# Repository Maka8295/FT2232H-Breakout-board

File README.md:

# Bill of Materials

**Line items:** 28  |  **Total components:** 70

> Pin header connectors (J2–J12) are excluded from this BOM.

## IC

| Designator | Value / Part | Footprint | Qty |
|---|---|---|---|
| U1 | LDK130M18R | `SOT-23-5` | 1 |
| U2 | LDK130M25R | `SOT-23-5` | 1 |
| U3 | AP2112K-3.3 | `SOT-23-5` | 1 |
| U4 | USBLC6-2SC6 | `SOT-23-6` | 1 |
| U5 | 93LCxxBxxOT | `SOT-23-6` | 1 |
| U6 | FT2232HL | `LQFP-64_10x10mm_P0.5mm` | 1 |
| U7, U8 | TMUX1574DYY | `Texas_DYY0016A_TSOT-23-16_2x4.2mm_P0.5mm` | 2 |
| U9, U10 | SN74LVC8T245PWR | `TSSOP-24_4.4x7.8mm_P0.65mm` | 2 |

## Connector

| Designator | Value / Part | Footprint | Qty |
|---|---|---|---|
| J1 | USB_A | `USB_A_CNCTech_1001-011-01101_Horizontal` | 1 |

## Resistor

| Designator | Value / Part | Footprint | Qty |
|---|---|---|---|
| R1 | 2.2k | `R_0603_1608Metric_Pad0.98x0.95mm` | 1 |
| R2, R3, R5 | 1k | `R_0603_1608Metric_Pad0.98x0.95mm` | 3 |
| R4 | 1M | `R_0603_1608Metric_Pad0.98x0.95mm` | 1 |
| R6 | 12k/1% | `R_0603_1608Metric_Pad0.98x0.95mm` | 1 |
| R7, R8, R9, R10 | 4.7k | `R_0603_1608Metric_Pad0.98x0.95mm` | 4 |
| R11, R12, R13 | 10k | `R_0603_1608Metric_Pad0.98x0.95mm` | 3 |
| R14 | 2k | `R_0603_1608Metric_Pad0.98x0.95mm` | 1 |

## Capacitor

| Designator | Value / Part | Footprint | Qty |
|---|---|---|---|
| C1, C2, C3, C4, C5, C6 | 1uF | `C_0603_1608Metric_Pad1.08x0.95mm` | 6 |
| C7 | 2.2nF | `C_0603_1608Metric_Pad1.08x0.95mm` | 1 |
| C8, C10 | 10nF | `C_0603_1608Metric_Pad1.08x0.95mm` | 2 |
| C9 | 100nF | `C_0603_1608Metric_Pad1.08x0.95mm` | 1 |
| C11, C12, C13, C14, C15, C18, C19, C20, C22, C24, C27, C28, C29, C31, C33, C34, C35, C36, C37, C39 | 0.1uF | `C_0603_1608Metric_Pad1.08x0.95mm` | 20 |
| C16 | 0.01uF | `C_0603_1608Metric_Pad1.08x0.95mm` | 1 |
| C17, C21, C23, C30, C32, C38 | 4.7uF | `C_0603_1608Metric_Pad1.08x0.95mm` | 6 |

## Inductor

| Designator | Value / Part | Footprint | Qty |
|---|---|---|---|
| L1, L2, L3 | 600R/0.5A | `L_0603_1608Metric_Pad1.05x0.95mm` | 3 |

## Transistor/MOSFET

| Designator | Value / Part | Footprint | Qty |
|---|---|---|---|
| Q1 | AO3400A | `SOT-23` | 1 |

## LED

| Designator | Value / Part | Footprint | Qty |
|---|---|---|---|
| D1, D2 | LED | `LED_0603_1608Metric` | 2 |

## Crystal

| Designator | Value / Part | Footprint | Qty |
|---|---|---|---|
| Y1 | SCTF SX3M12.000M20F30TNN | `Crystal_SMD_3225-4Pin_3.2x2.5mm_HandSoldering` | 1 |

## Switch

| Designator | Value / Part | Footprint | Qty |
|---|---|---|---|
| SW1 | Reset Button | `SW_Push_1P1T_NO_CK_KMR2` | 1 |

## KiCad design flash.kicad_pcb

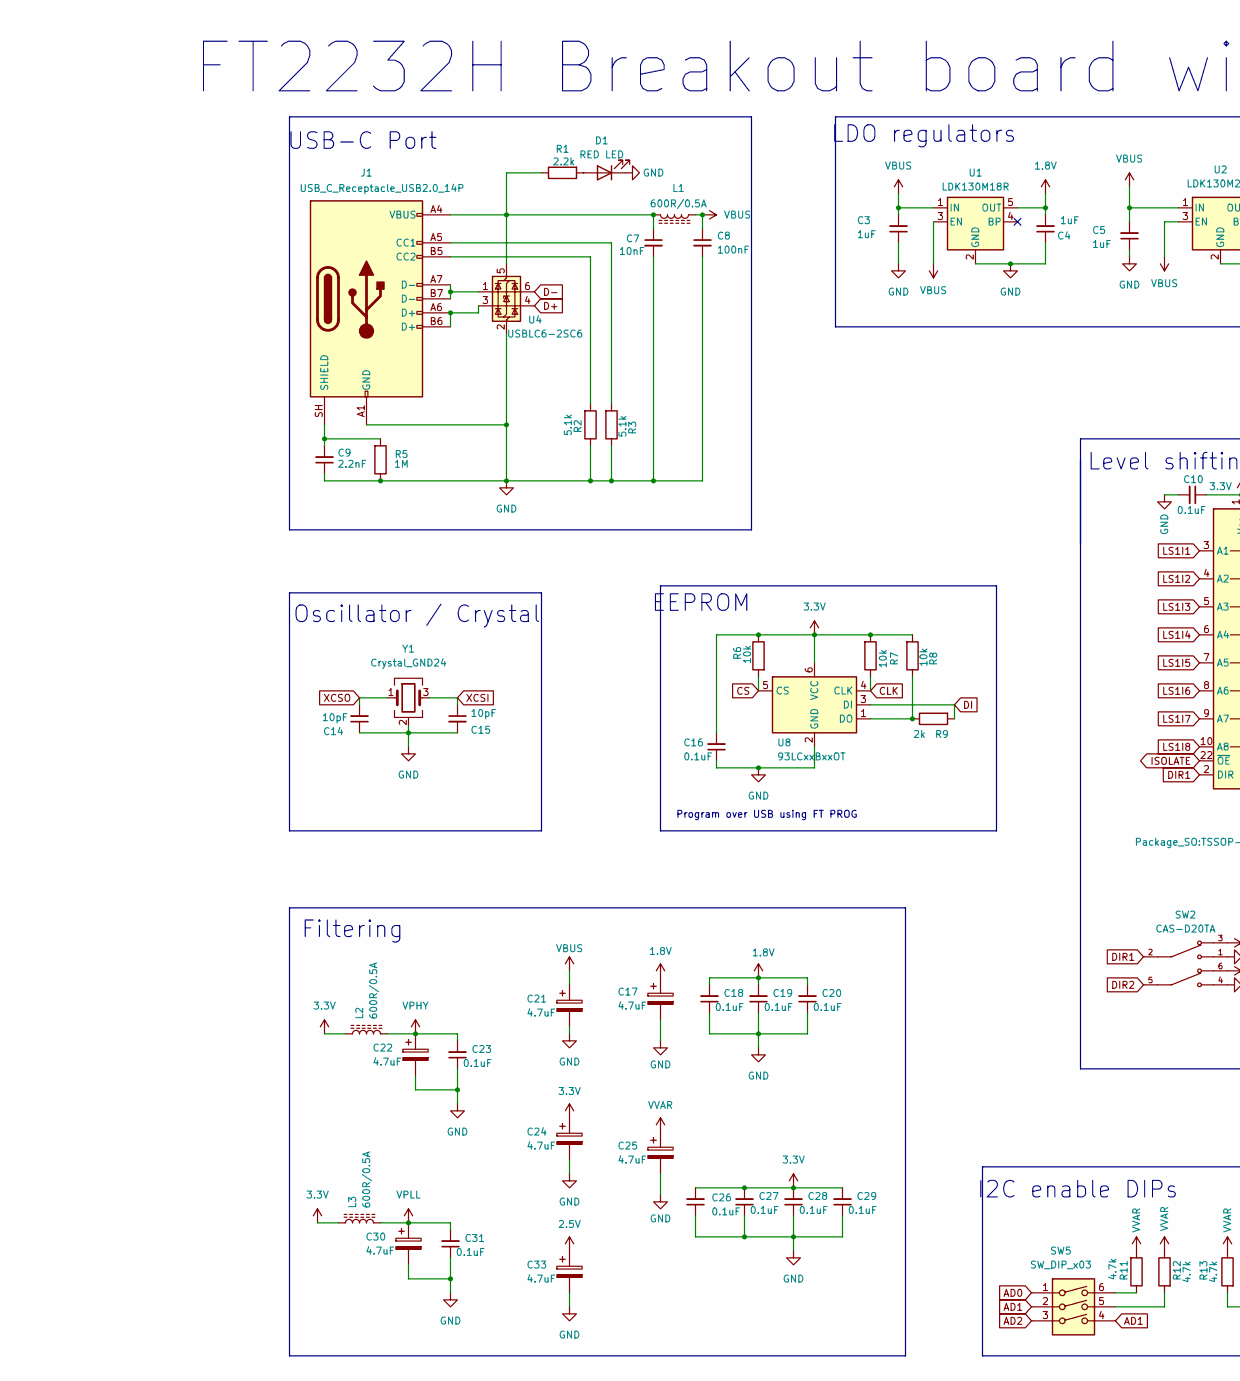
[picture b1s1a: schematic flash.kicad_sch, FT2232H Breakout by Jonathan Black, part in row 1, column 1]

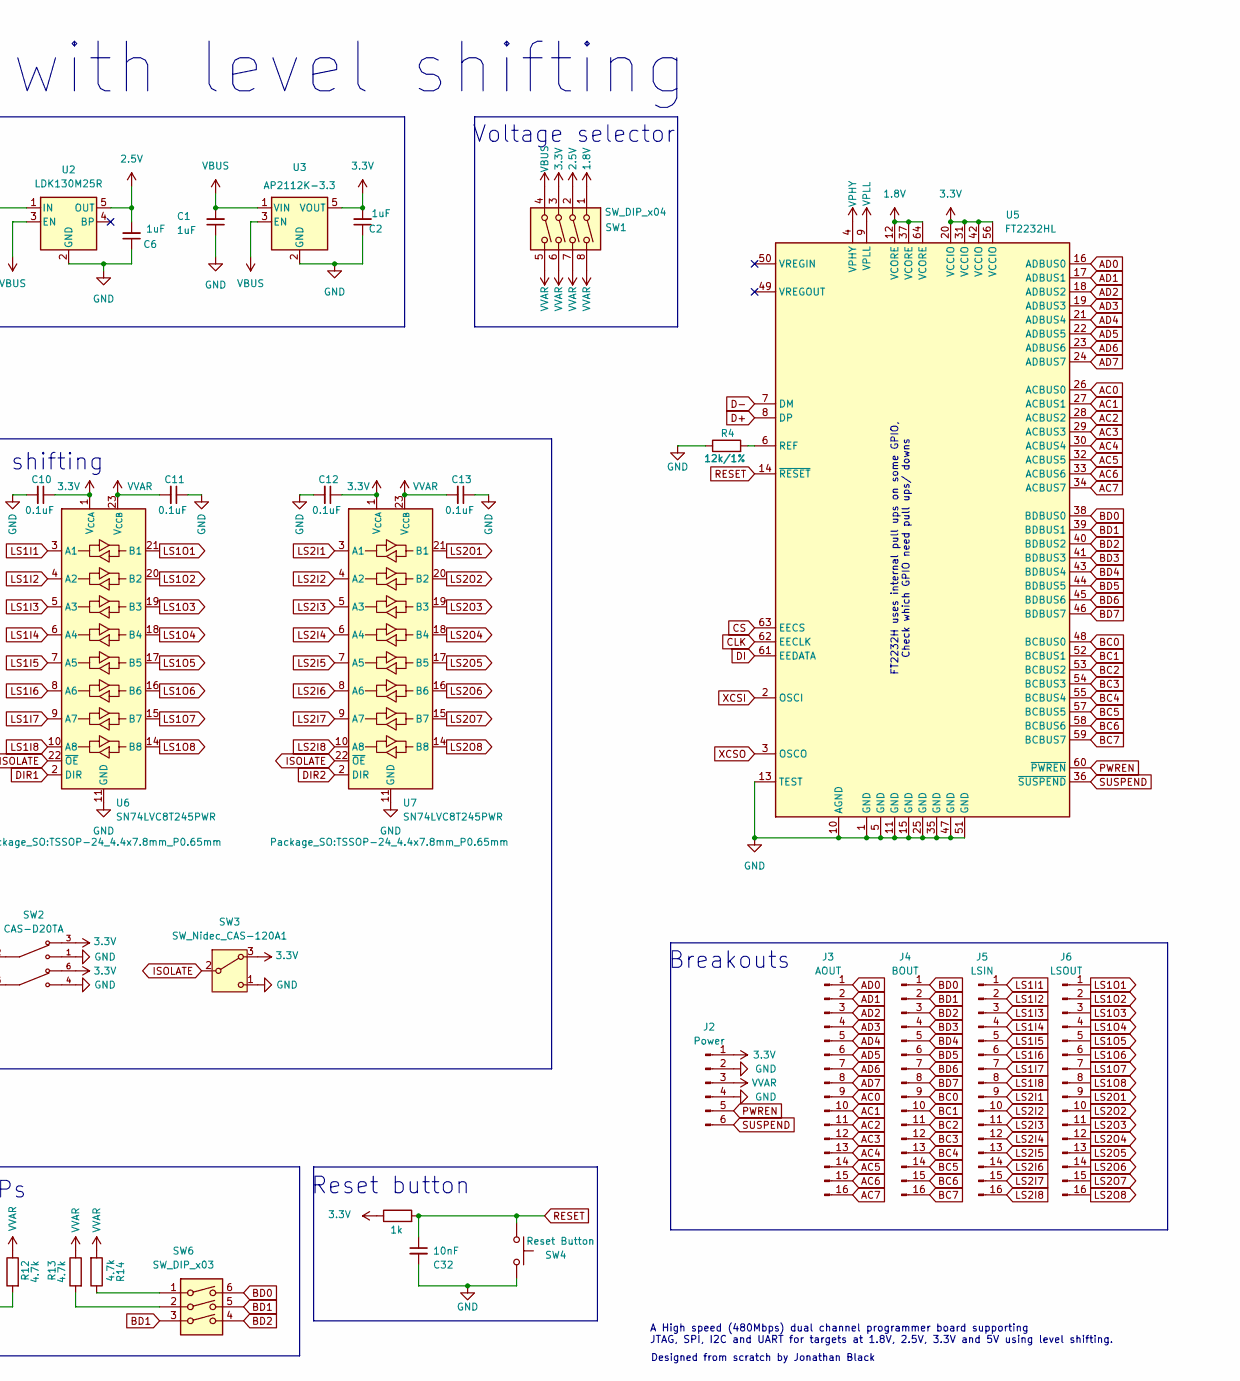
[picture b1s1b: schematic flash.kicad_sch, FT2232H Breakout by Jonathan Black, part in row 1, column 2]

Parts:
C1, C2, C3, C4, C5, C6: 1uF; C_0603_1608Metric_Pad1.08x0.95mm_HandSolder
C7, C32: 10nF; C_0603_1608Metric_Pad1.08x0.95mm_HandSolder
C8: 100nF; C_0603_1608Metric_Pad1.08x0.95mm_HandSolder
C9: 2.2nF; C_0603_1608Metric_Pad1.08x0.95mm_HandSolder
C10, C11, C12, C13, C16, C18, C19, C20, C23, C26, C27, C28, C29, C31: 0.1uF; C_0603_1608Metric_Pad1.08x0.95mm_HandSolder
C14, C15: 10pF; C_0603_1608Metric_Pad1.08x0.95mm_HandSolder
C17, C21, C22, C24, C25, C30, C33: 4.7uF; C_0603_1608Metric_Pad1.08x0.95mm_HandSolder
D1: RED LED; LED_0603_1608Metric
J1: USB_C_Receptacle_USB2.0_14P; USB_C_Receptacle_HRO_TYPE-C-31-M-12
J2: Power; PinHeader_2x03_P2.54mm_Vertical
J3: AOUT; PinHeader_1x16_P2.54mm_Vertical
J4: BOUT; PinHeader_1x16_P2.54mm_Vertical
J5: LSIN; PinHeader_2x08_P2.54mm_Vertical
J6: LSOUT; PinHeader_2x08_P2.54mm_Vertical
L1, L2, L3: 600R/0.5A; L_0603_1608Metric_Pad1.05x0.95mm_HandSolder
R1: 2.2k; R_0603_1608Metric_Pad0.98x0.95mm_HandSolder
R2, R3: 5.1k; R_0603_1608Metric_Pad0.98x0.95mm_HandSolder
R4: 12k/1%; R_0603_1608Metric_Pad0.98x0.95mm_HandSolder
R5: 1M; R_0603_1608Metric_Pad0.98x0.95mm_HandSolder
R6, R7, R8: 10k; R_0603_1608Metric_Pad0.98x0.95mm_HandSolder
R9: 2k; R_0603_1608Metric_Pad0.98x0.95mm_HandSolder
R10: 1k; R_0603_1608Metric_Pad0.98x0.95mm_HandSolder
R11, R12, R13, R14: 4.7k; R_0603_1608Metric_Pad0.98x0.95mm_HandSolder
SW1: SW_DIP_x04; SW_DIP_SPSTx04_Slide_Copal_CHS-04A_W5.08mm_P1.27mm_JPin
SW2: CAS-D20TA; SW_CAS-D20TA; PARTREV N/A
SW3: SW_Nidec_CAS-120A1; Nidec_Copal_CAS-120A
SW4: Reset Button; SW_Push_1P1T_NO_CK_KMR2
SW5, SW6: SW_DIP_x03; SW_DIP_SPSTx03_Slide_KingTek_DSHP03TJ_W5.25mm_P1.27mm_JPin
U1: LDK130M18R; SOT-23-5
U2: LDK130M25R; SOT-23-5
U3: AP2112K-3.3; SOT-23-5
U4: USBLC6-2SC6; SOT-23-6
U5: FT2232HL; LQFP-64_10x10mm_P0.5mm
U6, U7: SN74LVC8T245PWR; TSSOP-24_4.4x7.8mm_P0.65mm
U8: 93LCxxBxxOT; SOT-23-6
Y1: Crystal_GND24; Crystal_SMD_3225-4Pin_3.2x2.5mm_HandSoldering

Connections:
1.8V: C4.2, C17.1, C18.2, C19.2, C20.2, SW1.1, U1.5 (OUT), U5.12 (VCORE), U5.37 (VCORE), U5.64 (VCORE)
2.5V: C6.2, C33.1, SW1.2, U2.5 (OUT)
3.3V: C2.2, C10.1, C12.1, C16.2, C24.1, C26.2, C27.2, C28.2, C29.2, J2.1, L2.1, L3.1, R6.1, R7.2, R8.2, R10.1, SW1.3, SW2.3, SW2.6, SW3.3 (A), U3.5 (VOUT), U5.20 (VCCIO), U5.31 (VCCIO), U5.42 (VCCIO), U5.56 (VCCIO), U6.1 (V_{CCA}), U7.1 (V_{CCA}), U8.6 (VCC)
AC0: J3.9, U5.26 (ACBUS0)
AC1: J3.10, U5.27 (ACBUS1)
AC2: J3.11, U5.28 (ACBUS2)
AC3: J3.12, U5.29 (ACBUS3)
AC4: J3.13, U5.30 (ACBUS4)
AC5: J3.14, U5.32 (ACBUS5)
AC6: J3.15, U5.33 (ACBUS6)
AC7: J3.16, U5.34 (ACBUS7)
AD0: J3.1, SW5.1, U5.16 (ADBUS0)
AD1: J3.2, SW5.2, SW5.4, U5.17 (ADBUS1)
AD2: J3.3, SW5.3, U5.18 (ADBUS2)
AD3: J3.4, U5.19 (ADBUS3)
AD4: J3.5, U5.21 (ADBUS4)
AD5: J3.6, U5.22 (ADBUS5)
AD6: J3.7, U5.23 (ADBUS6)
AD7: J3.8, U5.24 (ADBUS7)
BC0: J4.9, U5.48 (BCBUS0)
BC1: J4.10, U5.52 (BCBUS1)
BC2: J4.11, U5.53 (BCBUS2)
BC3: J4.12, U5.54 (BCBUS3)
BC4: J4.13, U5.55 (BCBUS4)
BC5: J4.14, U5.57 (BCBUS5)
BC6: J4.15, U5.58 (BCBUS6)
BC7: J4.16, U5.59 (BCBUS7)
BD0: J4.1, SW6.6, U5.38 (BDBUS0)
BD1: J4.2, SW6.3, SW6.5, U5.39 (BDBUS1)
BD2: J4.3, SW6.4, U5.40 (BDBUS2)
BD3: J4.4, U5.41 (BDBUS3)
BD4: J4.5, U5.43 (BDBUS4)
BD5: J4.6, U5.44 (BDBUS5)
BD6: J4.7, U5.45 (BDBUS6)
BD7: J4.8, U5.46 (BDBUS7)
CLK: R7.1, U5.62 (EECLK), U8.4 (CLK)
CS: R6.2, U5.63 (EECS), U8.5 (CS)
D+: U4.4 (I/O2), U5.8 (DP)
D-: U4.6 (I/O1), U5.7 (DM)
DI: R9.2, U5.61 (EEDATA), U8.3 (DI)
DIR1: SW2.2, U6.2 (DIR)
DIR2: SW2.5, U7.2 (DIR)
GND: C1.1, C2.1, C3.1, C4.1, C5.1, C6.1, C7.2, C8.2, C9.1, C10.2, C11.1, C12.2, C13.1, C14.1, C15.2, C16.1, C17.2, C18.1, C19.1, C20.1, C21.2, C22.2, C23.1, C24.2, C25.2, C26.1, C27.1, C28.1, C29.1, C30.2, C31.1, C32.2, C33.2, D1.1 (K), J1.A1 (GND), J1.A12 (GND), J1.B1 (GND), J1.B12 (GND), J2.2, J2.4, R2.1, R3.1, R4.1, R5.1, SW2.1, SW2.4, SW3.1 (C), SW4.2, U1.2 (GND), U2.2 (GND), U3.2 (GND), U4.2 (GND), U5.1 (GND), U5.5 (GND), U5.10 (AGND), U5.11 (GND), U5.13 (TEST), U5.15 (GND), U5.25 (GND), U5.35 (GND), U5.47 (GND), U5.51 (GND), U6.11 (GND), U6.12 (GND), U6.13 (GND), U7.11 (GND), U7.12 (GND), U7.13 (GND), U8.2 (GND), Y1.2 (G), Y1.4 (G)
ISOLATE: SW3.2 (B), U6.22 (~OE), U7.22 (~OE)
LS1I1: J5.1, U6.3 (A1)
LS1I2: J5.2, U6.4 (A2)
LS1I3: J5.3, U6.5 (A3)
LS1I4: J5.4, U6.6 (A4)
LS1I5: J5.5, U6.7 (A5)
LS1I6: J5.6, U6.8 (A6)
LS1I7: J5.7, U6.9 (A7)
LS1I8: J5.8, U6.10 (A8)
LS1O1: J6.1, U6.21 (B1)
LS1O2: J6.2, U6.20 (B2)
LS1O3: J6.3, U6.19 (B3)
LS1O4: J6.4, U6.18 (B4)
LS1O5: J6.5, U6.17 (B5)
LS1O6: J6.6, U6.16 (B6)
LS1O7: J6.7, U6.15 (B7)
LS1O8: J6.8, U6.14 (B8)
LS2I1: J5.9, U7.3 (A1)
LS2I2: J5.10, U7.4 (A2)
LS2I3: J5.11, U7.5 (A3)
LS2I4: J5.12, U7.6 (A4)
LS2I5: J5.13, U7.7 (A5)
LS2I6: J5.14, U7.8 (A6)
LS2I7: J5.15, U7.9 (A7)
LS2I8: J5.16, U7.10 (A8)
LS2O1: J6.9, U7.21 (B1)
LS2O2: J6.10, U7.20 (B2)
LS2O3: J6.11, U7.19 (B3)
LS2O4: J6.12, U7.18 (B4)
LS2O5: J6.13, U7.17 (B5)
LS2O6: J6.14, U7.16 (B6)
LS2O7: J6.15, U7.15 (B7)
LS2O8: J6.16, U7.14 (B8)
unnamed: D1.2 (A), R1.2
unnamed: J1.A5 (CC1), R3.2
unnamed: J1.B5 (CC2), R2.2
unnamed: J1.A6 (D+), J1.B6 (D+), U4.3 (I/O2)
unnamed: J1.A7 (D-), J1.B7 (D-), U4.1 (I/O1)
unnamed: C9.2, J1.SH (SHIELD), R5.2
unnamed: R11.1, SW5.6
unnamed: R12.2, SW5.5
unnamed: R13.2, SW6.2
unnamed: R14.1, SW6.1
unnamed: C7.1, J1.A4 (VBUS), J1.A9 (VBUS), J1.B4 (VBUS), J1.B9 (VBUS), L1.2, R1.1, U4.5 (VBUS)
unnamed: R4.2, U5.6 (REF)
unnamed: R8.1, R9.1, U8.1 (DO)
PWREN: J2.5, U5.60 (~PWREN)
RESET: C32.1, R10.2, SW4.1, U5.14 (~RESET)
SUSPEND: J2.6, U5.36 (~SUSPEND)
VBUS: C1.2, C3.2, C5.2, C8.1, C21.1, L1.1, SW1.4, U1.1 (IN), U1.3 (EN), U2.1 (IN), U2.3 (EN), U3.1 (VIN), U3.3 (EN)
VPHY: C22.1, C23.2, L2.2, U5.4 (VPHY)
VPLL: C30.1, C31.2, L3.2, U5.9 (VPLL)
VVAR: C11.2, C13.2, C25.1, J2.3, R11.2, R12.1, R13.1, R14.2, SW1.5, SW1.6, SW1.7, SW1.8, U6.23 (V_{CCB}), U6.24 (V_{CCB}), U7.23 (V_{CCB}), U7.24 (V_{CCB})
XCSI: C15.1, U5.2 (OSCI), Y1.3
XCSO: C14.2, U5.3 (OSCO), Y1.1

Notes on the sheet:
Breakouts
Level shifting
Reset button
I2C enable DIPs
FT2232H Breakout board with level shifting
FT2232H uses internal pull ups on some GPIO, Check which GPIO need pull ups/ downs
Designed from scratch by Jonathan Black
Filtering
USB-C Port
Voltage selector
Program over USB using FT PROG
A High speed (480Mbps) dual channel programmer board supporting JTAG, SPI, I2C and UART for targets at 1.8V, 2.5V, 3.3V and 5V using level shifting.
Oscillator / Crystal
EEPROM
LDO regulators

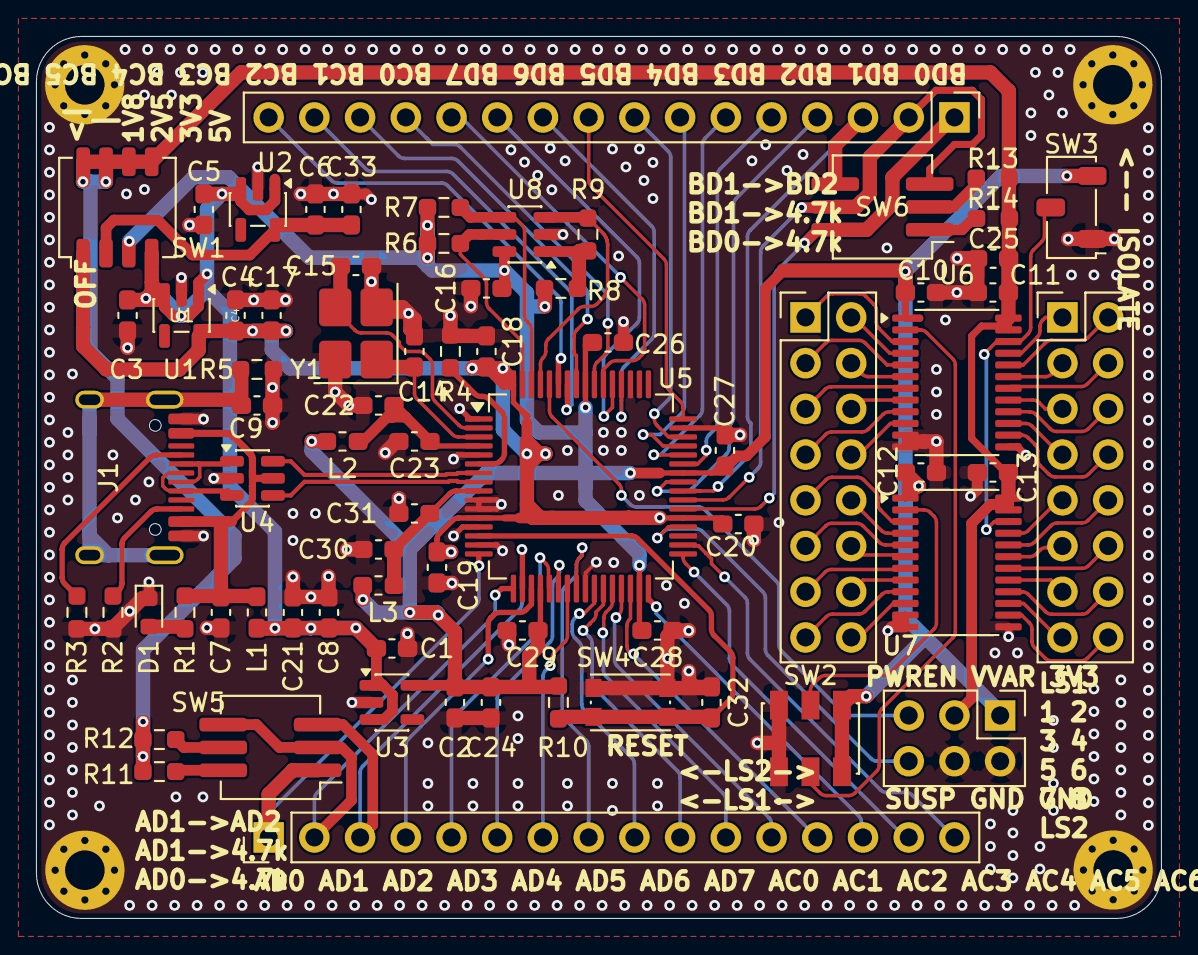
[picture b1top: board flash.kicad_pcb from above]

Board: 4 copper layers, 62.5 x 49.0 mm, 72 parts (0 on the bottom side), 98 nets.

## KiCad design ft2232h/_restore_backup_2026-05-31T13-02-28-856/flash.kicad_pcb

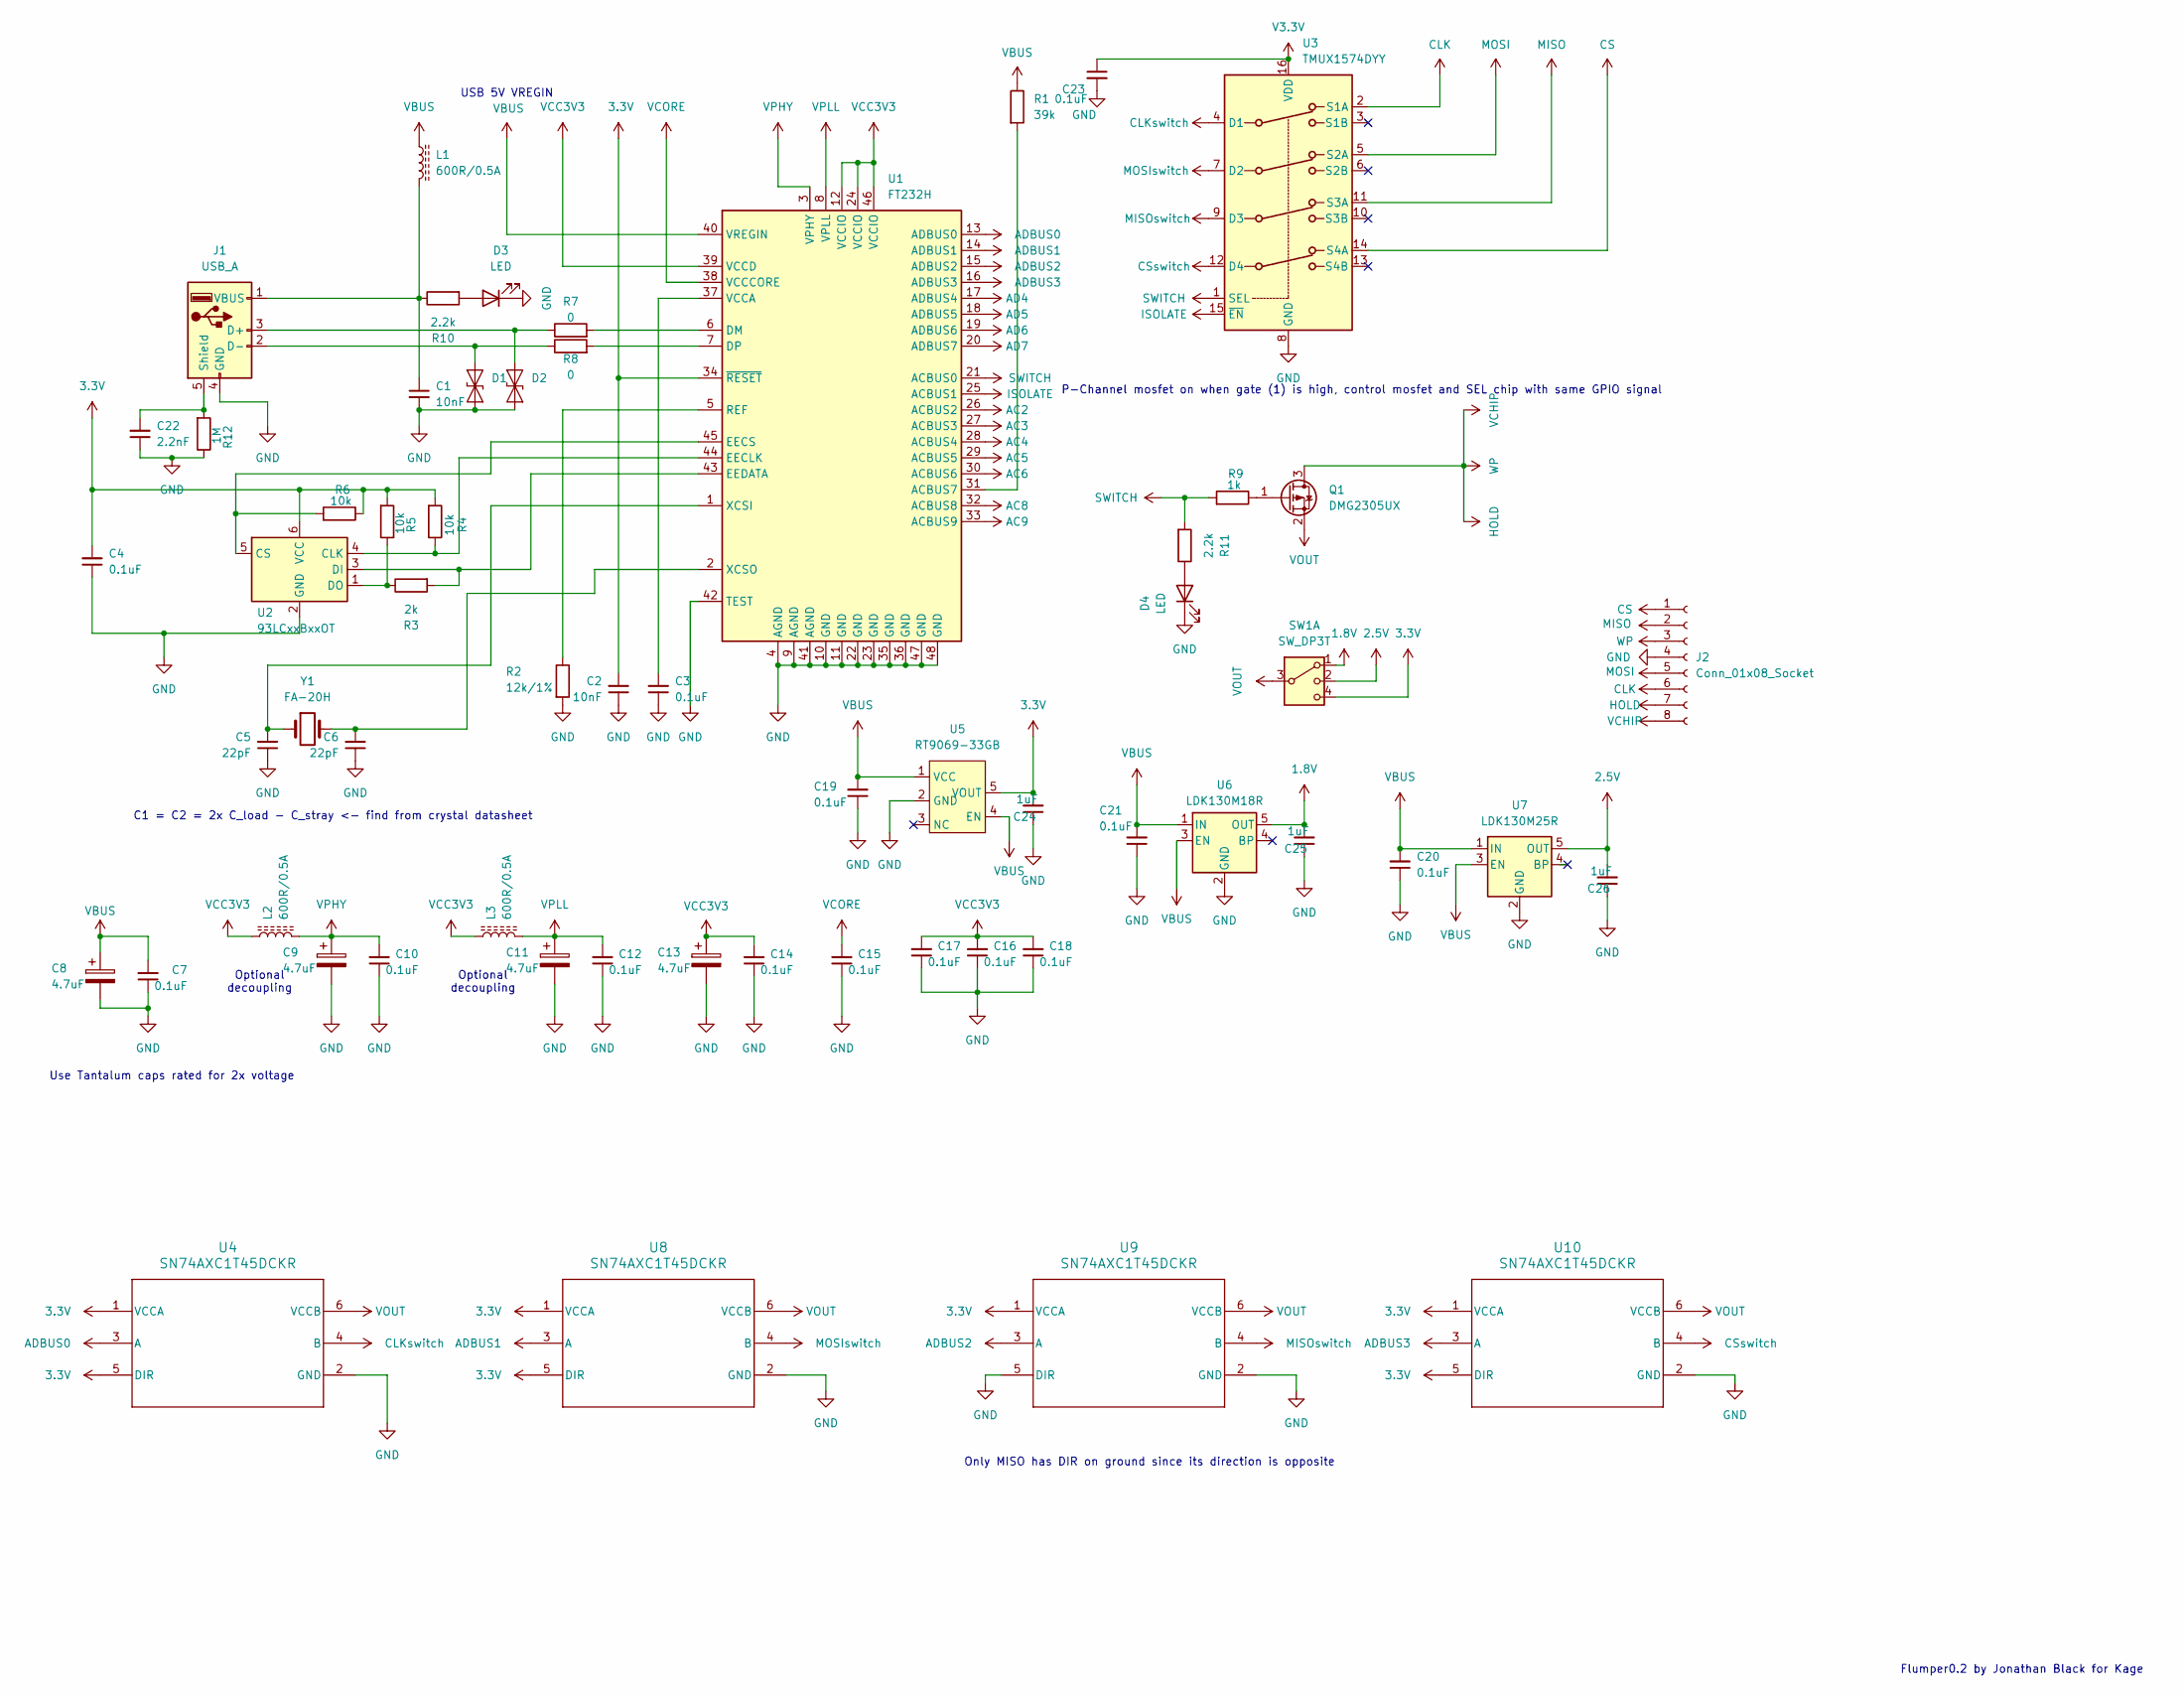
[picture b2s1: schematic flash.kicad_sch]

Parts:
C1, C2: 10nF; C_0201_0603Metric
C3, C4, C7, C10, C12, C14, C15, C16, C17, C18, C19, C20, C21, C23: 0.1uF; C_0201_0603Metric
C5, C6: 22pF; C_0201_0603Metric
C8, C9, C11, C13: 4.7uF; CP_EIA-3528-12_Kemet-T
C22: 2.2nF; C_0201_0603Metric
C24, C25, C26: 1uF; C_0201_0603Metric
D1, D2: D_SOD-923
D3, D4: LED; LED_0603_1608Metric
J1: USB_A; USB_A_CNCTech_1001-011-01101_Horizontal
J2: Conn_01x08_Socket; TE_1-84952-0_1x10-1MP_P1.0mm_Horizontal
L1, L2, L3: 600R/0.5A; L_0201_0603Metric
Q1: DMG2305UX; SOT-23
R1: 39k; R_0201_0603Metric
R2: 12k/1%; R_0201_0603Metric
R3: 2k; R_0201_0603Metric
R4, R5, R6: 10k; R_0201_0603Metric
R7, R8: 0; R_0201_0603Metric
R9: 1k; R_0201_0603Metric
R10, R11: 2.2k; R_0201_0603Metric
R12: 1M; R_0201_0603Metric
SW1: SW_DP3T
U1: FT232H; LQFP-48-1EP_7x7mm_P0.5mm_EP3.6x3.6mm
U2: 93LCxxBxxOT; SOT-23-6
U3: TMUX1574DYY; Texas_DYY0016A_TSOT-23-16_2x4.2mm_P0.5mm
U4, U8, U9, U10: SN74AXC1T45DCKR; DCK0006A_N
U5: RT9069-33GB; SOT-23-5
U6: LDK130M18R; SOT-23-5
U7: LDK130M25R; SOT-23-5
Y1: FA-20H; Crystal_SMD_3225-4Pin_3.2x2.5mm

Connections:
1.8V: C25.2, SW1.1, U6.5 (OUT); also elsewhere on the board
2.5V: C26.2, SW1.2, U7.5 (OUT); also elsewhere on the board
3.3V: C2.2, C4.2, C24.2, R4.2, R5.2, R6.1, SW1.4, U1.34 (~RESET), U2.6 (VCC), U4.1 (VCCA), U4.5 (DIR), U5.5 (VOUT), U8.1 (VCCA), U8.5 (DIR), U9.1 (VCCA), U10.1 (VCCA), U10.5 (DIR); also elsewhere on the board
AC2: U1.26 (ACBUS2); also elsewhere on the board
AC3: U1.27 (ACBUS3); also elsewhere on the board
AC4: U1.28 (ACBUS4); also elsewhere on the board
AC5: U1.29 (ACBUS5); also elsewhere on the board
AC6: U1.30 (ACBUS6); also elsewhere on the board
AC8: U1.32 (ACBUS8); also elsewhere on the board
AC9: U1.33 (ACBUS9); also elsewhere on the board
AD4: U1.17 (ADBUS4); also elsewhere on the board
AD5: U1.18 (ADBUS5); also elsewhere on the board
AD6: U1.19 (ADBUS6); also elsewhere on the board
AD7: U1.20 (ADBUS7); also elsewhere on the board
ADBUS0: U1.13 (ADBUS0), U4.3 (A)
ADBUS1: U1.14 (ADBUS1), U8.3 (A)
ADBUS2: U1.15 (ADBUS2), U9.3 (A)
ADBUS3: U1.16 (ADBUS3), U10.3 (A)
CLK: J2.6, U3.2 (S1A)
CLKswitch: U3.4 (D1), U4.4 (B)
CS: J2.1, U3.14 (S4A)
CSswitch: U3.12 (D4), U10.4 (B)
GND: C1.2, C2.1, C3.1, C4.1, C5.1, C6.1, C7.1, C8.2, C9.2, C10.1, C11.2, C12.1, C13.2, C14.1, C15.1, C16.1, C17.1, C18.1, C19.1, C20.1, C21.1, C22.1, C23.2, C24.1, C25.1, C26.1, D1.1 (A1), D2.1 (A1), D3.1 (K), D4.1 (K), J1.4 (GND), J2.4, R2.2, R12.1, U1.4 (AGND), U1.9 (AGND), U1.10 (GND), U1.11 (GND), U1.22 (GND), U1.23 (GND), U1.35 (GND), U1.36 (GND), U1.41 (AGND), U1.42 (TEST), U1.47 (GND), U1.48 (GND), U2.2 (GND), U3.8 (GND), U4.2 (GND), U5.2 (GND), U6.2 (GND), U7.2 (GND), U8.2 (GND), U9.2 (GND), U9.5 (DIR), U10.2 (GND)
HOLD: J2.3, J2.7, J2.8, Q1.3 (D)
ISOLATE: U1.25 (ACBUS1), U3.15 (~EN)
MISO: J2.2, U3.11 (S3A)
MISOswitch: U3.9 (D3), U9.4 (B)
MOSI: J2.5, U3.5 (S2A)
MOSIswitch: U3.7 (D2), U8.4 (B)
unnamed: D1.2 (A2), J1.2 (D-), R8.1
unnamed: D2.2 (A2), J1.3 (D+), R7.1
unnamed: D3.2 (A), R10.2
unnamed: D4.2 (A), R11.1
unnamed: C22.2, J1.5 (Shield), R12.2
unnamed: C1.1, J1.1 (VBUS), L1.2, R10.1
unnamed: Q1.1 (G), R9.1
unnamed: R1.2, U1.31 (ACBUS7)
unnamed: R7.2, U1.6 (DM)
unnamed: R8.2, U1.7 (DP)
unnamed: R4.1, U1.44 (EECLK), U2.4 (CLK)
unnamed: R6.2, U1.45 (EECS), U2.5 (CS)
unnamed: R3.2, U1.43 (EEDATA), U2.3 (DI)
unnamed: R2.1, U1.5 (REF)
unnamed: C3.2, U1.37 (VCCA)
unnamed: C5.2, U1.1 (XCSI), Y1.1
unnamed: C6.2, U1.2 (XCSO), Y1.2
unnamed: R3.1, R5.1, U2.1 (DO)
SWITCH: R9.2, R11.2, U1.21 (ACBUS0), U3.1 (SEL)
V3.3V: C23.1, U3.16 (VDD)
VBUS: C7.2, C8.1, C19.2, C20.2, C21.2, L1.1, R1.1, U1.40 (VREGIN), U5.1 (VCC), U5.4 (EN), U6.1 (IN), U6.3 (EN), U7.1 (IN), U7.3 (EN)
VCC3V3: C13.1, C14.2, C16.2, C17.2, C18.2, L2.1, L3.1, U1.12 (VCCIO), U1.24 (VCCIO), U1.39 (VCCD), U1.46 (VCCIO)
VCORE: C15.2, U1.38 (VCCCORE)
VOUT: Q1.2 (S), SW1.3, U4.6 (VCCB), U8.6 (VCCB), U9.6 (VCCB), U10.6 (VCCB); also elsewhere on the board
VPHY: C9.1, C10.2, L2.2, U1.3 (VPHY)
VPLL: C11.1, C12.2, L3.2, U1.8 (VPLL)

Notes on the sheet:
Only MISO has DIR on ground since its direction is opposite
Flumper0.2 by Jonathan Black for Kage
Use Tantalum caps rated for 2x voltage
P-Channel mosfet on when gate (1) is high, control mosfet and SEL chip with same GPIO signal
USB 5V VREGIN
Optional decoupling
C1 = C2 = 2x C_load - C_stray <- find from crystal datasheet
Optional decoupling

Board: 4 copper layers, 62 parts (5 on the bottom side), 55 nets, no tracks yet.

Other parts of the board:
1.8 2.5 3.3 Voltage: PinHeader_2x03_P2.54mm_Vertical
AC 4  5  6  8  9: PinHeader_1x05_P2.54mm_Vertical
AD  4  5  6  7 | 2  3  AC: PinHeader_1x06_P2.54mm_Vertical

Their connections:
1.8V: 1.8 2.5 3.3 Voltage.1; also elsewhere on the board
2.5V: 1.8 2.5 3.3 Voltage.3; also elsewhere on the board
3.3V: 1.8 2.5 3.3 Voltage.5; also elsewhere on the board
AC2: AD 4 5 6 7 | 2 3 AC.5; also elsewhere on the board
AC3: AD 4 5 6 7 | 2 3 AC.6; also elsewhere on the board
AC4: AC 4 5 6 8 9.1; also elsewhere on the board
AC5: AC 4 5 6 8 9.2; also elsewhere on the board
AC6: AC 4 5 6 8 9.3; also elsewhere on the board
AC8: AC 4 5 6 8 9.4; also elsewhere on the board
AC9: AC 4 5 6 8 9.5; also elsewhere on the board
AD4: AD 4 5 6 7 | 2 3 AC.1; also elsewhere on the board
AD5: AD 4 5 6 7 | 2 3 AC.2; also elsewhere on the board
AD6: AD 4 5 6 7 | 2 3 AC.3; also elsewhere on the board
AD7: AD 4 5 6 7 | 2 3 AC.4; also elsewhere on the board
VOUT: 1.8 2.5 3.3 Voltage.2, 1.8 2.5 3.3 Voltage.4, 1.8 2.5 3.3 Voltage.6; also elsewhere on the board

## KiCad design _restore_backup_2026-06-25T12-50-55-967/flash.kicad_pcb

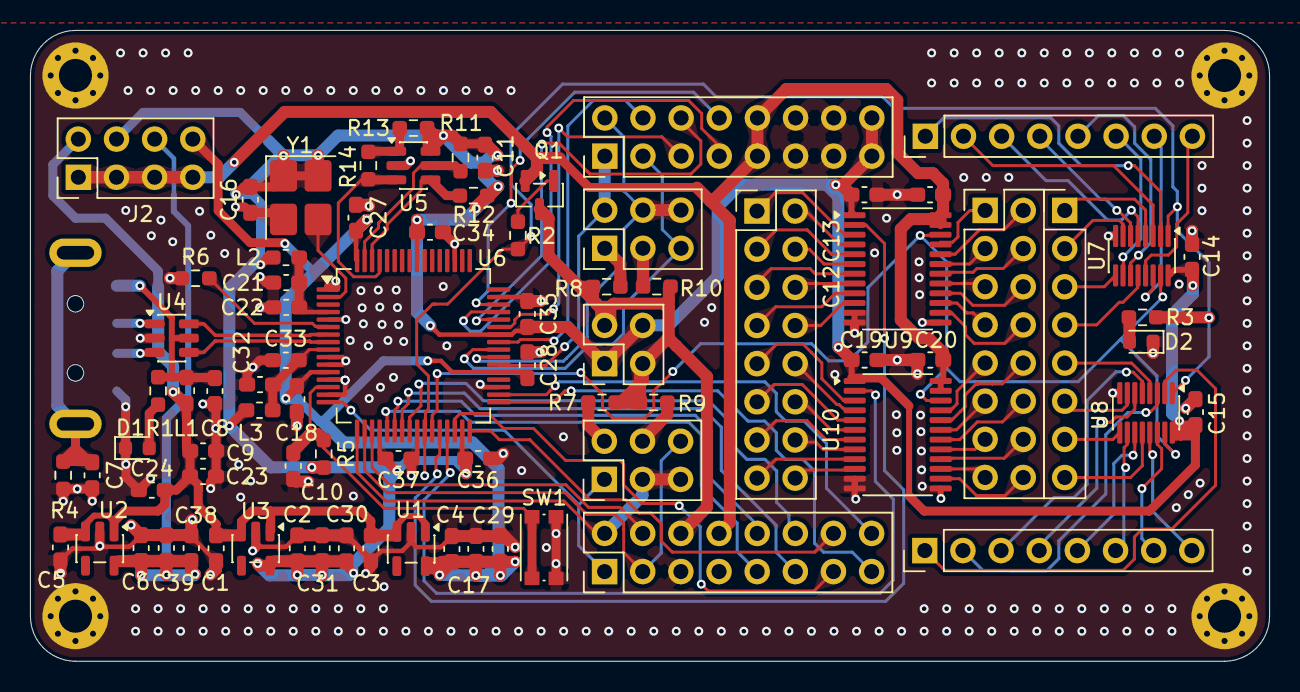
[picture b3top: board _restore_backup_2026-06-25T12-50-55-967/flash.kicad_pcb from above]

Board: 4 copper layers, 82.5 x 42.0 mm, 81 parts (1 on the bottom side), 109 nets.

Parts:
C1, C2, C3, C4, C5, C6: 1uF; C_0603_1608Metric_Pad1.08x0.95mm_HandSolder
C7: 2.2nF; C_0603_1608Metric_Pad1.08x0.95mm_HandSolder
C8, C10: 10nF; C_0603_1608Metric_Pad1.08x0.95mm_HandSolder
C9: 100nF; C_0603_1608Metric_Pad1.08x0.95mm_HandSolder
C11, C12, C13, C14, C15, C18, C19, C20, C22, C24, C27, C28, C29, C31, C33, C34, C35, C36, C37, C39: 0.1uF; C_0603_1608Metric_Pad1.08x0.95mm_HandSolder
C16: 0.01uF; C_0603_1608Metric_Pad1.08x0.95mm_HandSolder
C17, C21, C23, C30, C32, C38: 4.7uF; C_0603_1608Metric_Pad1.08x0.95mm_HandSolder
D1, D2: LED; LED_0603_1608Metric
J1: USB_A; USB_A_CNCTech_1001-011-01101_Horizontal
J2: Conn_01x08_Pin; PinHeader_2x04_P2.54mm_Vertical
J3, J4: Conn_01x06_Pin; PinHeader_2x03_P2.54mm_Vertical
J5: Conn_01x04_Pin; PinHeader_2x02_P2.54mm_Vertical
J6: AOUT; PinHeader_2x08_P2.54mm_Vertical
J7: BOUT; PinHeader_2x08_P2.54mm_Vertical
J8: LSIN; PinHeader_2x08_P2.54mm_Vertical
J9: LSOUT; PinHeader_2x08_P2.54mm_Vertical
J10: TMIN; PinHeader_1x08_P2.54mm_Vertical
J11: TM1OUT; PinHeader_1x08_P2.54mm_Vertical
J12: TM2OUT; PinHeader_1x08_P2.54mm_Vertical
L1, L2, L3: 600R/0.5A; L_0603_1608Metric_Pad1.05x0.95mm_HandSolder
Q1: AO3400A; SOT-23
R1: 2.2k; R_0603_1608Metric_Pad0.98x0.95mm_HandSolder
R2, R3, R5: 1k; R_0603_1608Metric_Pad0.98x0.95mm_HandSolder
R4: 1M; R_0603_1608Metric_Pad0.98x0.95mm_HandSolder
R6: 12k/1%; R_0603_1608Metric_Pad0.98x0.95mm_HandSolder
R7, R8, R9, R10: 4.7k; R_0603_1608Metric_Pad0.98x0.95mm_HandSolder
R11, R12, R13: 10k; R_0603_1608Metric_Pad0.98x0.95mm_HandSolder
R14: 2k; R_0603_1608Metric_Pad0.98x0.95mm_HandSolder
SW1: Reset Button; SW_Push_1P1T_NO_CK_KMR2
U1: LDK130M18R; SOT-23-5
U2: LDK130M25R; SOT-23-5
U3: AP2112K-3.3; SOT-23-5
U4: USBLC6-2SC6; SOT-23-6
U5: 93LCxxBxxOT; SOT-23-6
U6: FT2232HL; LQFP-64_10x10mm_P0.5mm
U7, U8: TMUX1574DYY; Texas_DYY0016A_TSOT-23-16_2x4.2mm_P0.5mm
U9, U10: SN74LVC8T245PWR; TSSOP-24_4.4x7.8mm_P0.65mm
Y1: SCTF SX3M12.000M20F30TNN; Crystal_SMD_3225-4Pin_3.2x2.5mm_HandSoldering

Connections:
1.8V: C4.2, C17.1, C18.2, C27.2, C28.2, C29.2, J2.8, U1.5 (OUT), U6.12 (VCORE), U6.37 (VCORE), U6.64 (VCORE)
2.5V: C6.2, C38.1, C39.2, J2.6, U2.5 (OUT)
3.3V: C2.2, C11.2, C12.1, C14.1, C15.1, C16.2, C19.1, C30.1, C31.2, C34.2, C35.2, C36.2, C37.2, J2.4, J5.1, J5.4, J7.15, J7.16, L2.1, L3.1, R5.1, R11.1, R12.2, R13.2, U3.5 (VOUT), U5.6 (VCC), U6.20 (VCCIO), U6.31 (VCCIO), U6.42 (VCCIO), U6.56 (VCCIO), U7.16 (VDD), U8.16 (VDD), U9.1 (V_{CCA}), U10.1 (V_{CCA}), Y1.1 (EN), Y1.4 (V+)
AC4: J6.13, U6.30 (ACBUS4)
AC5: J6.14, U6.32 (ACBUS5)
AC6: J6.15, U6.33 (ACBUS6)
AC7: J6.16, U6.34 (ACBUS7)
AD0: J3.1, J6.1, U6.16 (ADBUS0)
AD1: J3.3, J3.5, J6.2, U6.17 (ADBUS1)
AD2: J3.6, J6.3, U6.18 (ADBUS2)
AD3: J6.4, U6.19 (ADBUS3)
AD4: J6.9, U6.21 (ADBUS4)
AD5: J6.10, U6.22 (ADBUS5)
AD6: J6.11, U6.23 (ADBUS6)
AD7: J6.12, U6.24 (ADBUS7)
BD0: J4.2, J7.1, U6.38 (BDBUS0)
BD1: J4.4, J4.6, J7.2, U6.39 (BDBUS1)
BD2: J4.5, J7.3, U6.40 (BDBUS2)
BD3: J7.4, U6.41 (BDBUS3)
BD4: J7.5, U6.43 (BDBUS4)
BD5: J7.6, U6.44 (BDBUS5)
BD6: J7.7, U6.45 (BDBUS6)
BD7: J7.8, U6.46 (BDBUS7)
CLK: R12.1, U5.4 (CLK), U6.62 (EECLK)
CS: R11.2, U5.5 (CS), U6.63 (EECS)
D+: U4.4 (I/O2), U6.8 (DP)
D-: U4.6 (I/O1), U6.7 (DM)
DI: R14.2, U5.3 (DI), U6.61 (EEDATA)
DIR1: U6.28 (ACBUS2), U9.2 (DIR)
DIR2: U6.29 (ACBUS3), U10.2 (DIR)
GND: C1.1, C2.1, C3.1, C4.1, C5.1, C6.1, C7.1, C8.2, C9.2, C10.2, C11.1, C12.2, C13.1, C14.2, C15.2, C16.1, C17.2, C18.1, C19.2, C20.1, C21.2, C22.1, C23.2, C24.1, C27.1, C28.1, C29.1, C30.2, C31.1, C32.2, C33.1, C34.1, C35.1, C36.1, C37.1, C38.2, C39.1, D1.1 (K), D2.1 (K), J1.4 (GND), J6.5, J6.7, J7.11, J7.12, J7.13, J7.14, R4.1, R6.1, SW1.2, U1.2 (GND), U2.2 (GND), U3.2 (GND), U4.2 (GND), U5.2 (GND), U6.1 (GND), U6.5 (GND), U6.10 (AGND), U6.11 (GND), U6.13 (TEST), U6.15 (GND), U6.25 (GND), U6.35 (GND), U6.47 (GND), U6.51 (GND), U7.8 (GND), U8.8 (GND), U9.11 (GND), U9.12 (GND), U9.13 (GND), U10.11 (GND), U10.12 (GND), U10.13 (GND), Y1.2 (GND)
ISOLATE: U6.27 (ACBUS1), U7.15 (~EN), U8.15 (~EN), U9.22 (~OE), U10.22 (~OE)
LS1I1: J8.1, U9.3 (A1)
LS1I2: J8.2, U9.4 (A2)
LS1I3: J8.3, U9.5 (A3)
LS1I4: J8.4, U9.6 (A4)
LS1I5: J8.5, U9.7 (A5)
LS1I6: J8.6, U9.8 (A6)
LS1I7: J8.7, U9.9 (A7)
LS1I8: J8.8, U9.10 (A8)
LS1O1: J9.1, U9.21 (B1)
LS1O2: J9.2, U9.20 (B2)
LS1O3: J9.3, U9.19 (B3)
LS1O4: J9.4, U9.18 (B4)
LS1O5: J9.5, U9.17 (B5)
LS1O6: J9.6, U9.16 (B6)
LS1O7: J9.7, U9.15 (B7)
LS1O8: J9.8, U9.14 (B8)
LS2I1: J8.9, U10.3 (A1)
LS2I2: J8.10, U10.4 (A2)
LS2I3: J8.11, U10.5 (A3)
LS2I4: J8.12, U10.6 (A4)
LS2I5: J8.13, U10.7 (A5)
LS2I6: J8.14, U10.8 (A6)
LS2I7: J8.15, U10.9 (A7)
LS2I8: J8.16, U10.10 (A8)
LS2O1: J9.9, U10.21 (B1)
LS2O2: J9.10, U10.20 (B2)
LS2O3: J9.11, U10.19 (B3)
LS2O4: J9.12, U10.18 (B4)
LS2O5: J9.13, U10.17 (B5)
LS2O6: J9.14, U10.16 (B6)
LS2O7: J9.15, U10.15 (B7)
LS2O8: J9.16, U10.14 (B8)
unnamed: D1.2 (A), R1.2
unnamed: D2.2 (A), R3.1
unnamed: J1.3 (D+), U4.3 (I/O2)
unnamed: J1.2 (D-), U4.1 (I/O1)
unnamed: C7.2, J1.SH (Shield), R4.2
unnamed: C8.1, J1.1 (VBUS), L1.2, R1.1, U4.5 (VBUS)
unnamed: J3.2, R7.1
unnamed: J3.4, R9.2
unnamed: J4.1, R8.1
unnamed: J4.3, R10.2
unnamed: Q1.1 (G), R2.1
unnamed: R13.1, R14.1, U5.1 (DO)
REF: R6.2, U6.6 (REF)
RESET: C10.1, R5.2, SW1.1, U6.14 (~RESET)
SWITCH: R2.2, R3.2, U6.26 (ACBUS0), U7.1 (SEL), U8.1 (SEL)
TM1I1: J10.1, U7.4 (D1)
TM1I2: J10.2, U7.7 (D2)
TM1I3: J10.3, U7.9 (D3)
TM1I4: J10.4, U7.12 (D4)
TM1O1A: J11.1, U7.2 (S1A)
TM1O1B: J11.2, U7.3 (S1B)
TM1O2A: J11.3, U7.5 (S2A)
TM1O2B: J11.4, U7.6 (S2B)
TM1O3A: J11.5, U7.11 (S3A)
TM1O3B: J11.6, U7.10 (S3B)
TM1O4A: J11.7, U7.14 (S4A)
TM1O4B: J11.8, U7.13 (S4B)
TM2I1: J10.5, U8.4 (D1)
TM2I2: J10.6, U8.7 (D2)
TM2I3: J10.7, U8.9 (D3)
TM2I4: J10.8, U8.12 (D4)
TM2O1A: J12.1, U8.2 (S1A)
TM2O1B: J12.2, U8.3 (S1B)
TM2O2A: J12.3, U8.5 (S2A)
TM2O2B: J12.4, U8.6 (S2B)
TM2O3A: J12.5, U8.11 (S3A)
TM2O3B: J12.6, U8.10 (S3B)
TM2O4A: J12.7, U8.14 (S4A)
TM2O4B: J12.8, U8.13 (S4B)
VBUS: C1.2, C3.2, C5.2, C9.1, C23.1, C24.2, J2.2, L1.1, U1.1 (IN), U1.3 (EN), U2.1 (IN), U2.3 (EN), U3.1 (VIN), U3.3 (EN)
VOUT: J5.2, J5.3, J6.6, Q1.3 (D), R7.2, R8.2, R9.1, R10.1
VPHY: C21.1, C22.2, L2.2, U6.4 (VPHY)
VPLL: C32.1, C33.2, L3.2, U6.9 (VPLL)
VVAR: C13.2, C20.2, J2.1, J2.3, J2.5, J2.7, J6.8, J7.9, J7.10, Q1.2 (S), U9.23 (V_{CCB}), U9.24 (V_{CCB}), U10.23 (V_{CCB}), U10.24 (V_{CCB})
XCSI: U6.2 (OSCI), Y1.3 (OUT)

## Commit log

2026-06-28 init
2026-06-28 readme
2026-06-29 MondayAkiba
